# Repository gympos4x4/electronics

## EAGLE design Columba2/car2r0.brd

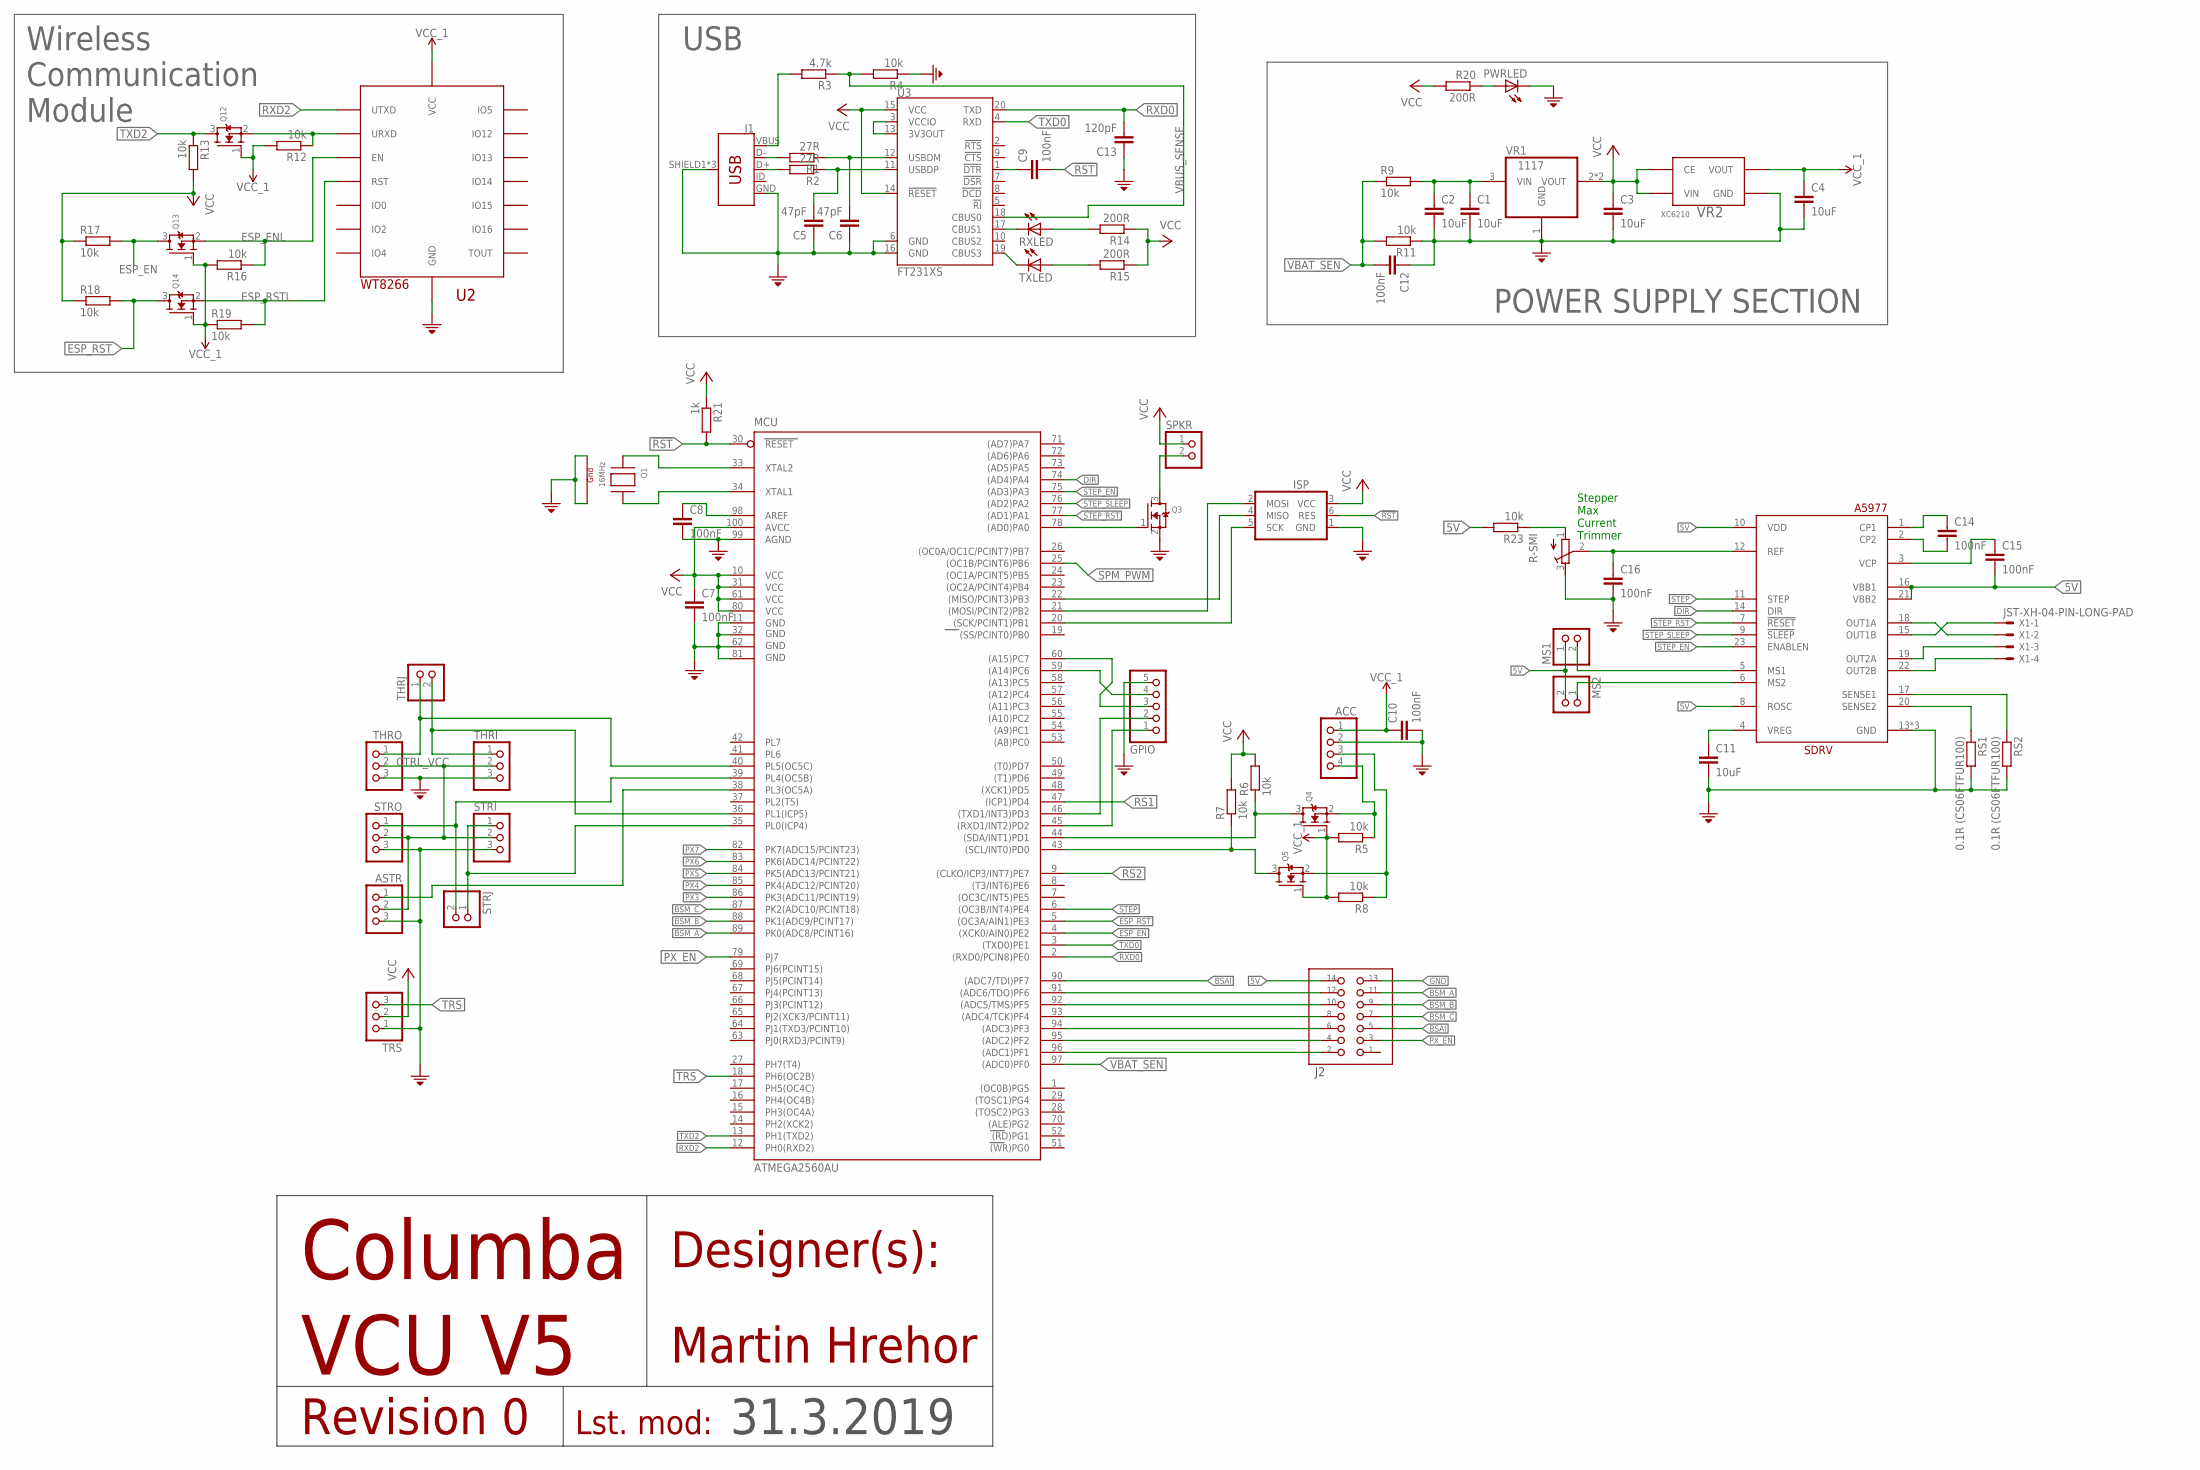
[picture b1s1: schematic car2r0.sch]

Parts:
ACC: PINHD-1X4/90; 1X04/90
ASTR: PINHD-1X3; 1X03
C1, C2, C3, C4, C11: 10uF; C1206
C5, C6: 47pF; C0603
C7, C8, C9, C10, C12, C14, C15, C16: 100nF; C1206
C13: 120pF; C0603
GPIO: PINHD-1X5; 1X05
ISP: ISP
J1: USB_MICRO-B_FEMALE-SMT; USB-B-MICRO-SMD
J2: DS1014-14S
MCU: ATMEGA2560AU; TQFP100
MS1, MS2: PINHD-1X2; 1X02
PWRLED: LEDCHIP-LED0603; CHIP-LED0603
Q1: 16MHz; NX3225
Q3, Q4, Q5, Q12, Q13, Q14: MOSFET-NREFLOW; SOT23
R1, R2: 27R; R0603
R3: 4.7k; R0603
R4, R5, R6, R7, R8, R12, R13, R16, R17, R18, R19, R23: 10k; R0603
R9, R11: 10k; R0805
R14, R15, R20: 200R; R0603
R21: 1k; R0603
R-SMI: R-TRIMM5W; RTRIM5W
RS1, RS2: 0.1R (CS06FTFUR100); R1206
RXLED: LEDCHIP-LED0603; CHIP-LED0603
SDRV: A4982LP; TSSOP24P
SPKR: PINHD-1X2; 1X02
STRI: PINHD-1X3; 1X03
STRJ: PINHD-1X2; 1X02
STRO: PINHD-1X3; 1X03
THRI: PINHD-1X3; 1X03
THRJ: PINHD-1X2; 1X02
THRO: PINHD-1X3; 1X03
TRS: PINHD-1X3; 1X03
TXLED: LEDCHIP-LED0603; CHIP-LED0603
U2: WT8266
U3: FT231XS; SSOP20_L
VR1: 1117; SOT223
VR2: XC6210; SOT25
X1: JST-XH-04-PIN-LONG-PAD; JST-XH-04-PACKAGE-LONG-PAD

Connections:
3V3: ACC.1, C4.1, C10.1, Q4.1 (G), Q5.1 (G), Q12.1 (G), Q13.1 (G), Q14.1 (G), R5.2, R8.2, R12.2, R16.2, R19.1, U2.3V3 (VCC), VR2.5 (VOUT)
5V: C3.1, C7.1, C15.2, ISP.3 (VCC), J2.P$14, MCU.10 (VCC), MCU.31 (VCC1), MCU.61 (VCC2), MCU.80 (VCC3), MCU.100 (AVCC), MS1.1, MS2.2, R6.2, R7.2, R13.2, R14.1, R15.1, R17.1, R18.1, R20.2, R21.1, R23.2, SDRV.8 (ROSC), SDRV.10 (VDD), SDRV.16 (VBB1), SDRV.21 (VBB2), SPKR.1, TRS.2, U3.14 (!RESET), U3.15 (VCC), VR1.2 (VOUT), VR1.4 (VOUT), VR2.1 (VIN), VR2.3 (CE)
!RST: C9.2, ISP.6 (RES), MCU.30 (RESET), R21.2
AREF: C8.1, MCU.98 (AREF)
ASTR: ASTR.1, MCU.38 (PL3(OC5A))
BSA0: J2.P$10, MCU.92 ((ADC5/TMS)PF5)
BSA1: J2.P$12, MCU.91 ((ADC6/TDO)PF6)
BSAI: J2.P$5, MCU.90 ((ADC7/TDI)PF7)
BSM_A: J2.P$11, MCU.89 (PK0(ADC8/PCINT16))
BSM_B: J2.P$9, MCU.88 (PK1(ADC9/PCINT17))
BSM_C: J2.P$7, MCU.87 (PK2(ADC10/PCINT18))
CP1: C14.1, SDRV.1 (CP1)
CP2: C14.2, SDRV.2 (CP2)
CTRL_VCC: ASTR.2, STRI.2, STRO.2, THRI.2, THRO.2
DIR: MCU.74 ((AD4)PA4), SDRV.14 (DIR)
DTR: C9.1, U3.1 (!DTR)
ESP_EN: MCU.4 ((XCK0/AIN0)PE2), Q13.3 (D), R17.2
ESP_ENL: Q13.2 (S), R16.1, U2.EN
ESP_RST: MCU.5 ((OC3A/AIN1)PE3), Q14.3 (D), R18.2
ESP_RSTL: Q14.2 (S), R19.2, U2.RST
GND: ACC.2, ASTR.3, C1.2, C2.2, C3.2, C4.2, C5.1, C6.1, C7.2, C8.2, C10.2, C11.2, C12.1, C13.1, C16.2, GPIO.5, ISP.1 (GND), J1.GND, J1.SHIELD1 (SHIELD), J1.SHIELD2 (SHIELD), J1.SHIELD3 (SHIELD), J2.P$13, MCU.11 (GND), MCU.32 (GND1), MCU.62 (GND2), MCU.81 (GND3), MCU.99 (AGND), PWRLED.C, Q1.2 (G2), Q1.4 (G1), Q3.2 (S), R4.1, R11.1, R-SMI.3 (E), RS1.2, RS2.2, SDRV.13 (GND), SDRV.24 (GND), SDRV.PAD (GND), STRI.3, STRO.3, THRI.3, THRO.3, TRS.1, U2.GND0 (GND), U2.GND1 (GND), U2.GND2 (GND), U3.6 (GND), U3.16 (GND), VR1.1 (GND), VR2.2 (GND)
LX0: J2.P$2, MCU.96 ((ADC1)PF1)
LX1: J2.P$4, MCU.95 ((ADC2)PF2)
LX2: J2.P$6, MCU.94 ((ADC3)PF3)
LX3: J2.P$8, MCU.93 ((ADC4/TCK)PF4)
MISO: ISP.4 (MISO), MCU.22 ((MISO/PCINT3)PB3)
MOSI: ISP.2 (MOSI), MCU.21 ((MOSI/PCINT2)PB2)
MS1: MS1.2, SDRV.5 (MS1)
MS2: MS2.1, SDRV.6 (MS2)
unnamed: MCU.33 (XTAL2), Q1.1 (X1)
unnamed: MCU.34 (XTAL1), Q1.3 (X2)
unnamed: GPIO.3, MCU.60 ((A15)PC7)
unnamed: GPIO.2, MCU.46 ((TXD1/INT3)PD3)
unnamed: GPIO.1, MCU.45 ((RXD1/INT2)PD2)
unnamed: PWRLED.A, R20.1
unnamed: GPIO.4, MCU.59 ((A14)PC6)
unnamed: R15.2, TXLED.A
unnamed: R14.2, RXLED.A
OUT1A: SDRV.18 (OUT1A), X1.2
OUT1B: SDRV.15 (OUT1B), X1.1
OUT2A: SDRV.19 (OUT2A), X1.3
OUT2B: SDRV.22 (OUT2B), X1.4
PX3: MCU.86 (PK3(ADC11/PCINT19))
PX4: MCU.85 (PK4(ADC12/PCINT20))
PX5: MCU.84 (PK5(ADC13/PCINT21))
PX6: MCU.83 (PK6(ADC14/PCINT22))
PX7: MCU.82 (PK7(ADC15/PCINT23))
PX_EN: J2.P$3, MCU.79 (PJ7)
RS1: MCU.47 ((ICP1)PD4)
RS2: MCU.9 ((CLKO/ICP3/INT7)PE7)
RXD0: C13.2, MCU.2 ((RXD0/PCIN8)PE0), U3.20 (TXD)
RXD2: MCU.12 (PH0(RXD2)), U2.UTXD
RXLED: RXLED.C, U3.17 (CBUS1)
SCK: ISP.5 (SCK), MCU.20 ((SCK/PCINT1)PB1)
SCL: MCU.43 ((SCL/INT0)PD0), Q5.3 (D), R7.1
SCLL: ACC.3, Q5.2 (S), R8.1
SDA: MCU.44 ((SDA/INT1)PD1), Q4.3 (D), R6.1
SDAL: ACC.4, Q4.2 (S), R5.1
SENSE1: RS2.1, SDRV.17 (SENSE1)
SENSE2: RS1.1, SDRV.20 (SENSE2)
SIV: R23.1, R-SMI.1 (A)
SPKR: MCU.78 ((AD0)PA0), Q3.1 (G)
SPKR0: Q3.3 (D), SPKR.2
SPM_PWM: MCU.25 ((OC1B/PCINT6)PB6)
STEP: MCU.6 ((OC3B/INT4)PE4), SDRV.11 (STEP)
STEP_EN: MCU.75 ((AD3)PA3), SDRV.23 (ENABLEN)
STEP_RST: MCU.77 ((AD1)PA1), SDRV.7 (!RESET)
STEP_SLEEP: MCU.76 ((AD2)PA2), SDRV.9 (!SLEEP)
STRI: MCU.35 (PL0(ICP4)), STRI.1, STRJ.1
STRO: MCU.39 (PL4(OC5B)), STRJ.2, STRO.1
SVREF: C16.1, R-SMI.2 (S), SDRV.12 (REF)
THRI: MCU.36 (PL1(ICP5)), THRI.1, THRJ.2
THRO: MCU.40 (PL5(OC5C)), THRJ.1, THRO.1
TRS: MCU.18 (PH6(OC2B)), TRS.3
TXD0: MCU.3 ((TXD0)PE1), U3.4 (RXD)
TXD2: MCU.13 (PH1(TXD2)), Q12.3 (D), R13.1
TXLED: TXLED.C, U3.19 (CBUS3)
URXD: Q12.2 (S), R12.1, U2.URXD
USBD+: J1.D+, R2.2
USBD-: J1.D-, R1.2
USBDM: C6.2, R1.1, U3.12 (USBDM)
USBDP: C5.2, R2.1, U3.11 (USBDP)
VBAT_SEN: C12.2, MCU.97 ((ADC0)PF0), R9.1, R11.2
VBUS: J1.VBUS, R3.2
VBUS_SENSE: R3.1, R4.2, U3.18 (CBUS0)
VCCIO: U3.3 (VCCIO), U3.13 (3V3OUT)
VCP: C15.1, SDRV.3 (VCP)
VIN: C1.1, C2.1, R9.2, VR1.3 (VIN)
VREG: C11.1, SDRV.4 (VREG)

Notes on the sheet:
POWER SUPPLY SECTION
Wireless Communication Module
USB
Columba
VCU V5
Revision 0
Designer(s):
Martin Hrehor
Lst. mod:
31.3.2019
Stepper Max Current Trimmer

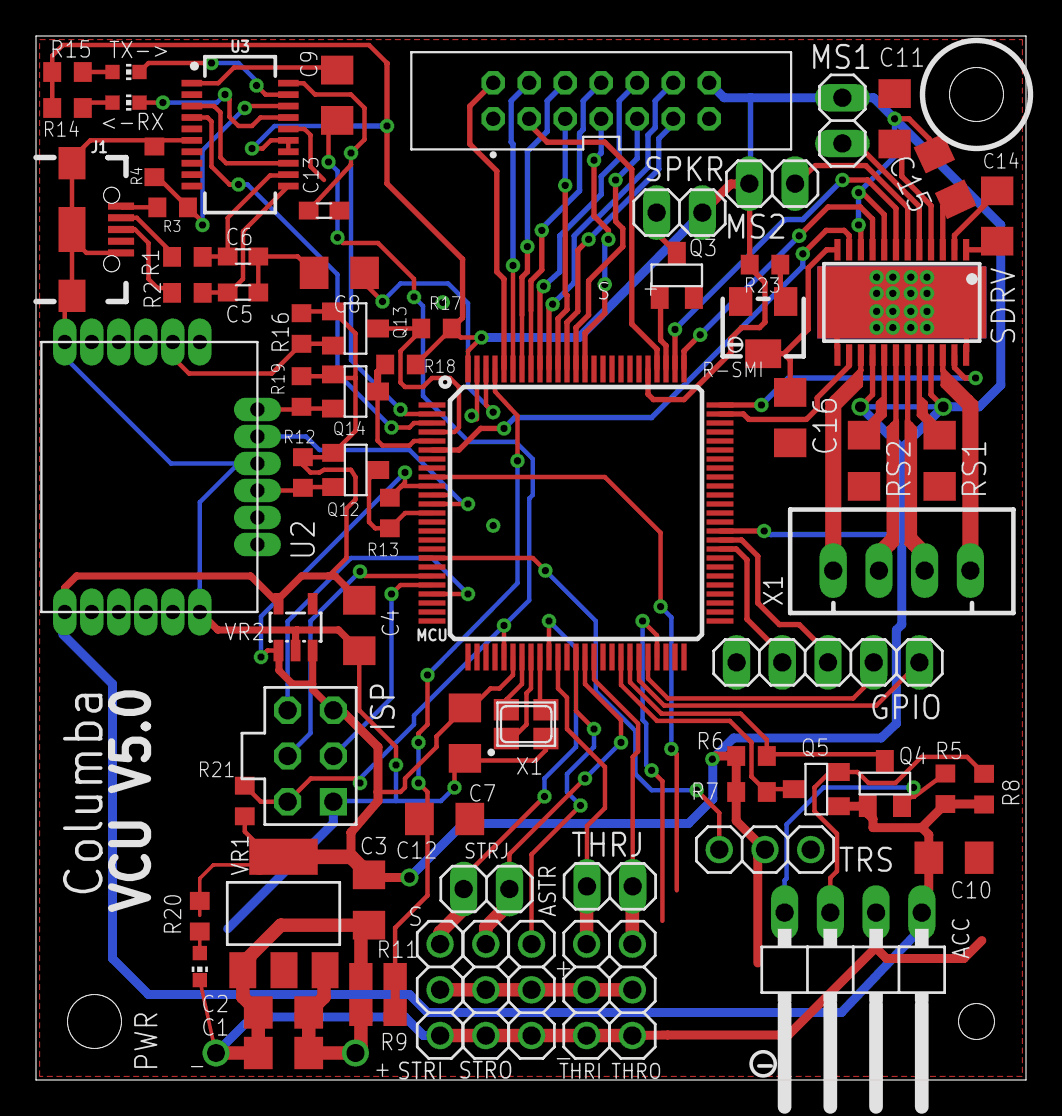
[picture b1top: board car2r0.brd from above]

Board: 2 copper layers, 55.0 x 58.0 mm, 73 parts (0 on the bottom side), 81 nets.

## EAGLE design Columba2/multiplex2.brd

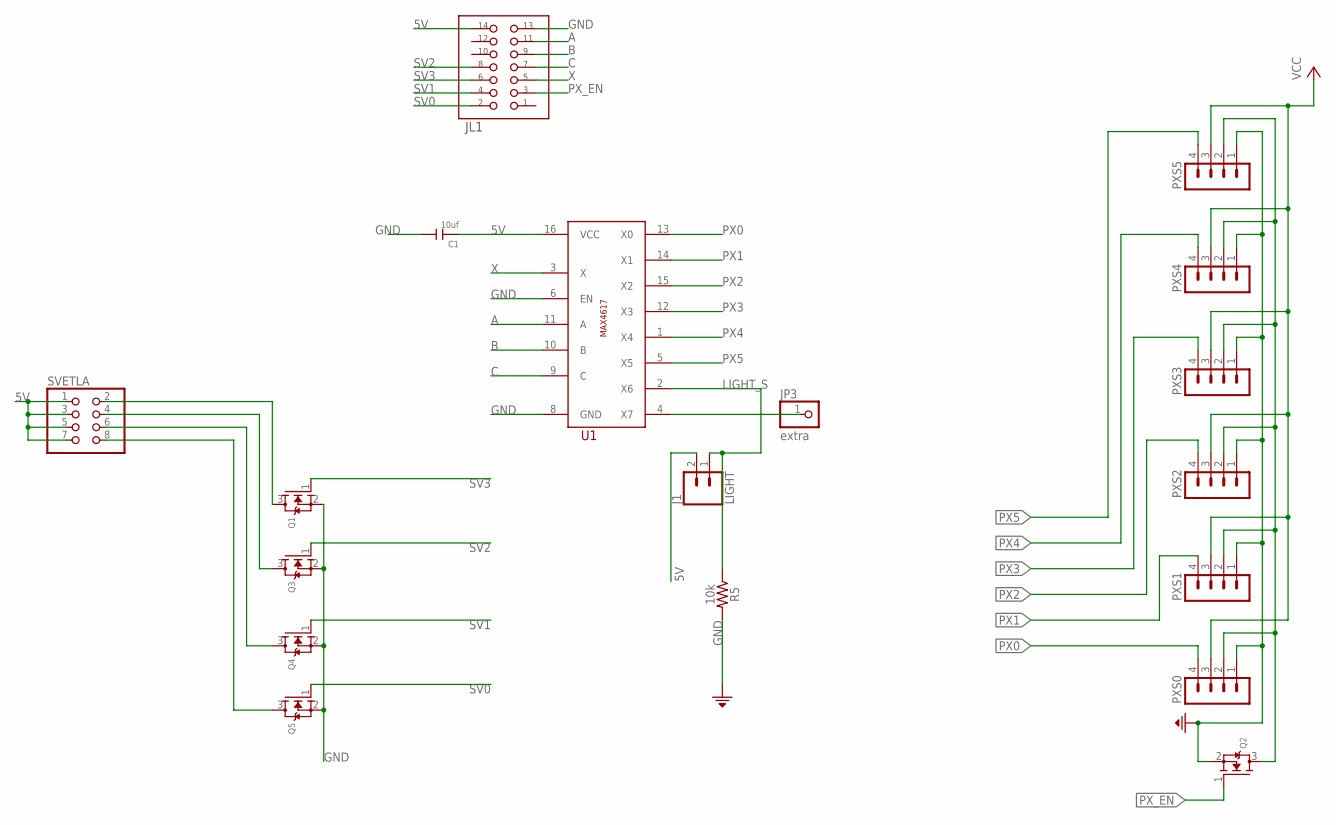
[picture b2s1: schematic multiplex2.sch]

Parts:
C1: 10uf; C1206
J1: LIGHT; 1X02
JL1: DS1014-14S
JP3: extra; 1X01
PXS0, PXS1, PXS2, PXS3, PXS4, PXS5: MA04-1
Q1, Q2, Q3, Q4, Q5: MOSFET-NREFLOW; SOT23
R5: 10k; 0603
SVETLA: PINHD-2X4; 2X04
U1: MAX4617CUE+T; TSSOP16

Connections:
5V: C1.1, J1.2, JL1.P$14, PXS0.3, PXS1.3, PXS2.3, PXS3.3, PXS4.3, PXS5.3, SVETLA.1, SVETLA.3, SVETLA.5, SVETLA.7, U1.16 (VCC)
A: JL1.P$11, U1.11 (A)
B: JL1.P$9, U1.10 (B)
C: JL1.P$7, U1.9 (C)
GND: C1.2, JL1.P$13, PXS0.1, PXS1.1, PXS2.1, PXS3.1, PXS4.1, PXS5.1, Q1.2 (S), Q2.2 (S), Q3.2 (S), Q4.2 (S), Q5.2 (S), R5.2, U1.6 (EN), U1.8 (GND)
LIGHT_S: J1.1, R5.1, U1.2 (X6)
unnamed: Q1.3 (D), SVETLA.2
unnamed: Q3.3 (D), SVETLA.4
unnamed: Q4.3 (D), SVETLA.6
unnamed: Q5.3 (D), SVETLA.8
unnamed: JP3.1, U1.4 (X7)
PX0: PXS0.4, U1.13 (X0)
PX1: PXS1.4, U1.14 (X1)
PX2: PXS2.4, U1.15 (X2)
PX3: PXS3.4, U1.12 (X3)
PX4: PXS4.4, U1.1 (X4)
PX5: PXS5.4, U1.5 (X5)
PXSO: PXS0.2, PXS1.2, PXS2.2, PXS3.2, PXS4.2, PXS5.2, Q2.3 (D)
PX_EN: JL1.P$3, Q2.1 (G)
SV0: JL1.P$2, Q5.1 (G)
SV1: JL1.P$4, Q4.1 (G)
SV2: JL1.P$8, Q3.1 (G)
SV3: JL1.P$6, Q1.1 (G)
X: JL1.P$5, U1.3 (X)

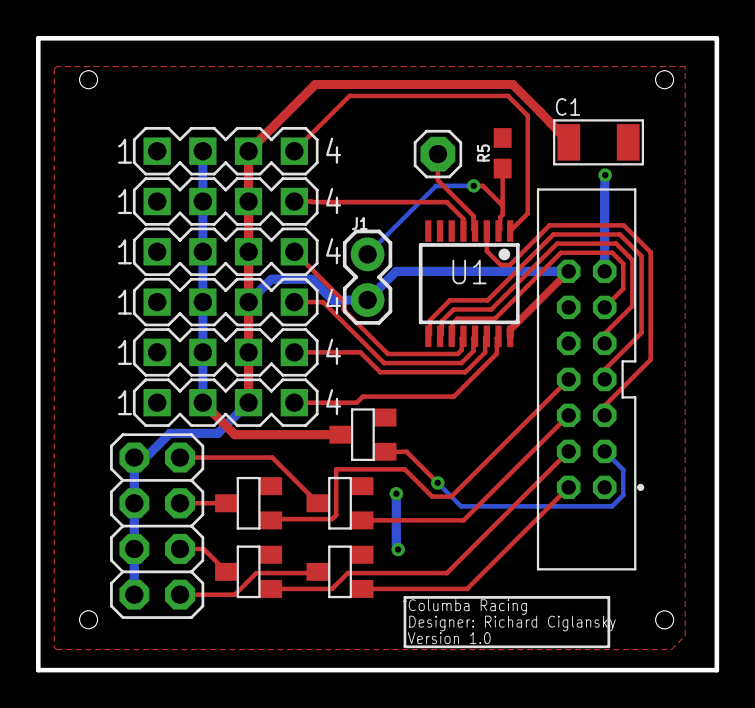
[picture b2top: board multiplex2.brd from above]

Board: 2 copper layers, 37.7 x 35.1 mm, 18 parts (0 on the bottom side), 24 nets.

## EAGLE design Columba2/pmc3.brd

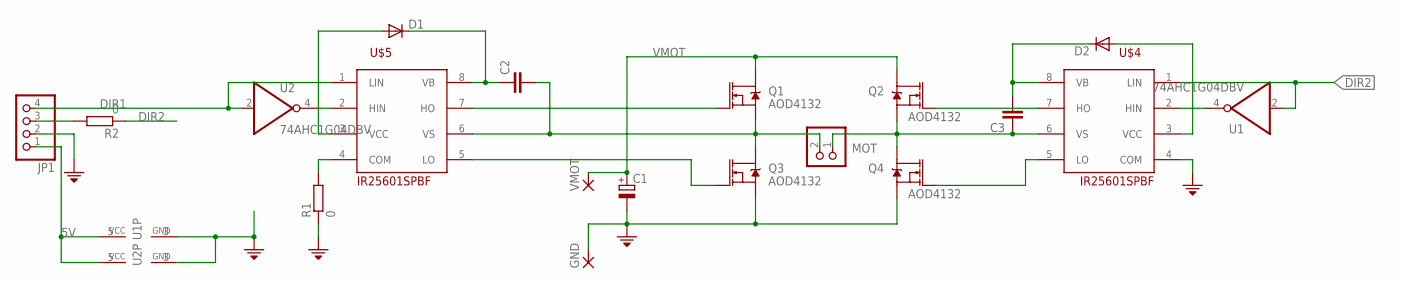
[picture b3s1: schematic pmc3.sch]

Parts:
C1: CPOL-EUE5-13; E5-13
C2, C3: C-EUC0805; C0805
D1, D2: DIODE-SOD123; SOD123
GND: SMD5; SMD2,54-5,08
JP1: PINHD-1X4/90; 1X04/90
MOT: PINHD-1X2; 1X02
Q1, Q2, Q3, Q4: AOD4132; DPAK
R1, R2: 0; R1206
U1, U2: 74AHC1G04DBV; SOT23-5
U$4, U$5: IR25601SPBF; SO08
VMOT: SMD5; SMD2,54-5,08

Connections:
5V: D1.A, D2.A, JP1.1, U1.5 (VCC), U2.5 (VCC), U$4.3 (VCC), U$5.3 (VCC)
D1O: C2.2, MOT.2, Q1.3 (S), Q3.4 (D), U$5.6 (VS)
D2O: C3.1, MOT.1, Q2.3 (S), Q4.4 (D), U$4.6 (VS)
DIR1: JP1.4, U2.2 (I), U$5.1 (LIN)
DIR2: R2.1, U1.2 (I), U$4.1 (LIN)
GND: C1.-, GND.1, JP1.2, Q3.3 (S), Q4.3 (S), R1.1, U1.3 (GND), U2.3 (GND), U$4.4 (COM)
unnamed: R1.2, U$5.4 (COM)
unnamed: JP1.3, R2.2
unnamed: Q3.1 (G), U$5.5 (LO)
unnamed: Q1.1 (G), U$5.7 (HO)
unnamed: U2.4 (O), U$5.2 (HIN)
unnamed: U1.4 (O), U$4.2 (HIN)
unnamed: Q4.1 (G), U$4.5 (LO)
unnamed: Q2.1 (G), U$4.7 (HO)
VBOOT1: C2.1, D1.C, U$5.8 (VB)
VBOOT2: C3.2, D2.C, U$4.8 (VB)
VMOT: C1.+, Q1.4 (D), Q2.4 (D), VMOT.1

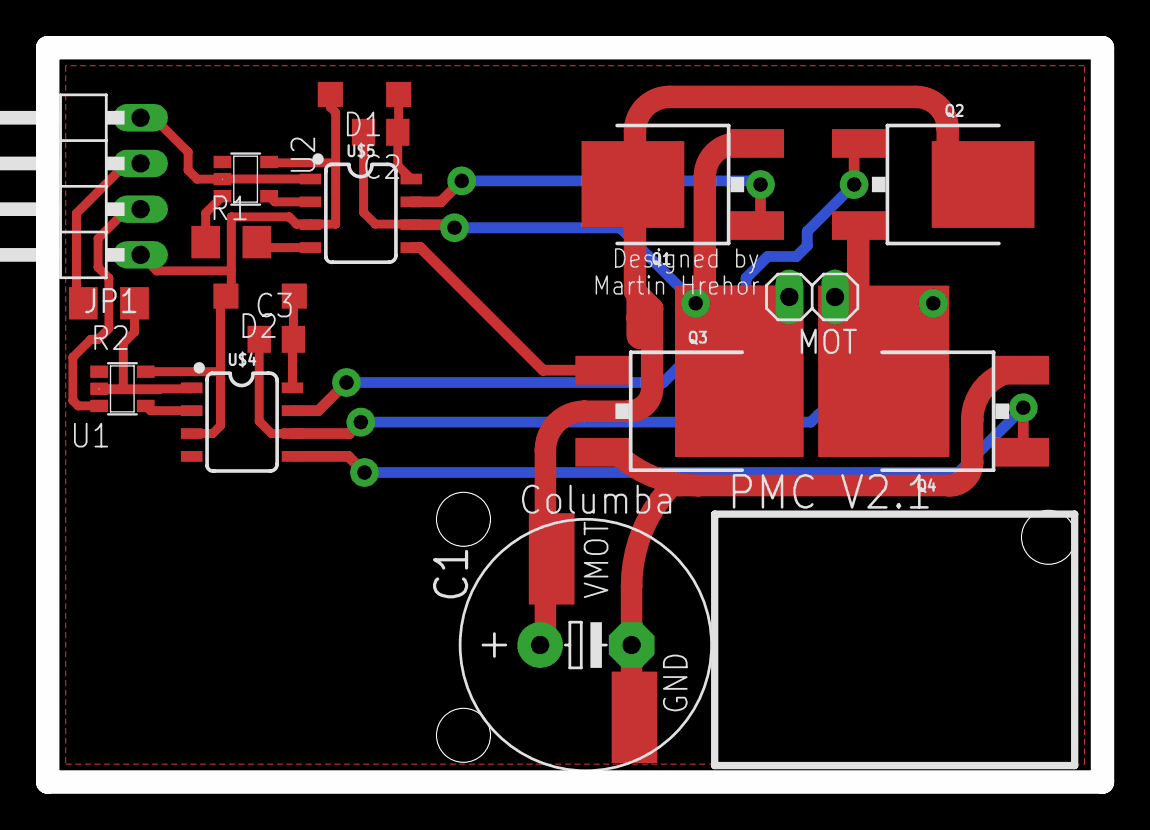
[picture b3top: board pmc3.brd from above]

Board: 2 copper layers, 58.6 x 40.8 mm, 19 parts (0 on the bottom side), 17 nets.

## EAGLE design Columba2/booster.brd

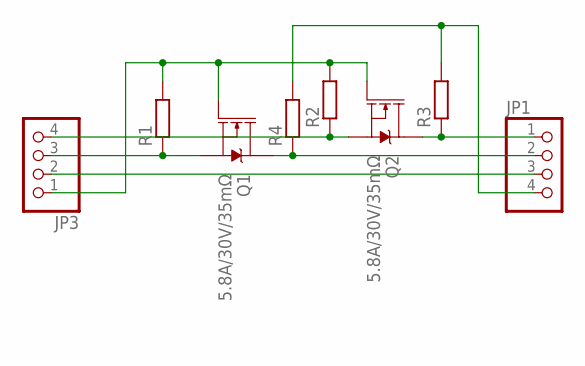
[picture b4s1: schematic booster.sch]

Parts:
JP1, JP3: PINHD-1X4/90; 1X04/90
Q1, Q2: 5.8A/30V/35mΩ; SOT23-3
R1, R2, R3, R4: R-EU_R0805; R0805

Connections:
unnamed: JP3.3, Q1.2 (S), R1.1
unnamed: JP1.2, Q1.3 (D), R4.1
unnamed: JP1.1, Q2.3 (D), R3.1
unnamed: JP3.4, Q2.2 (S), R2.1
unnamed: JP1.4, R3.2, R4.2
unnamed: JP1.3, JP3.2
unnamed: JP3.1, Q1.1 (G), Q2.1 (G), R1.2, R2.2

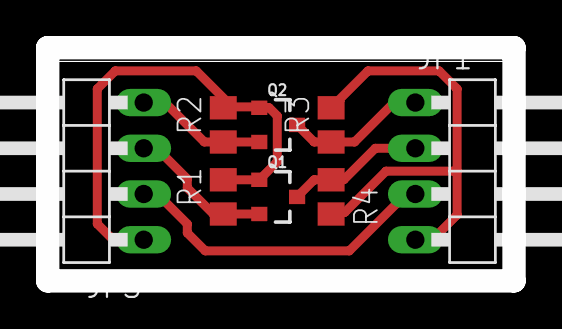
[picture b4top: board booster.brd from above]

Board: 2 copper layers, 25.9 x 13.0 mm, 8 parts (0 on the bottom side), 7 nets.

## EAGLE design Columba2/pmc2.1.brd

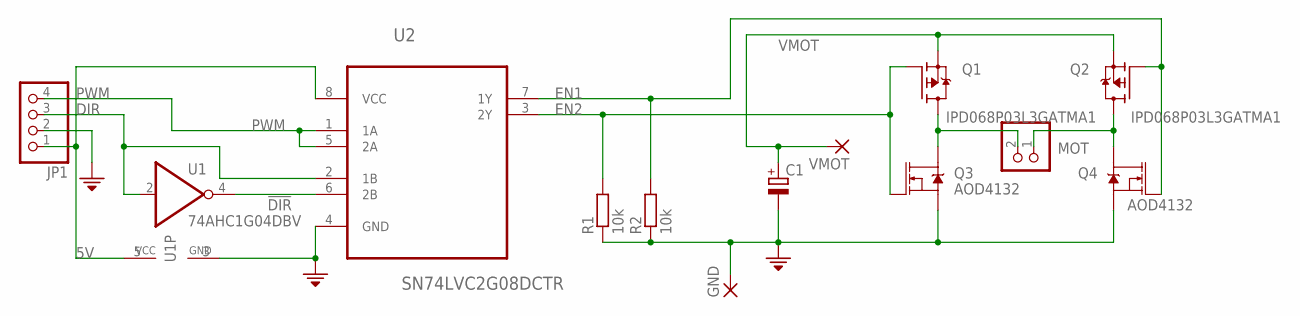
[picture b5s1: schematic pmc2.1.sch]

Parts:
C1: CPOL-EUE5-13; E5-13
GND: SMD5; SMD2,54-5,08
JP1: PINHD-1X4/90; 1X04/90
MOT: PINHD-1X2; 1X02
Q1, Q2: IPD068P03L3GATMA1; TO252
Q3, Q4: AOD4132; DPAK
R1, R2: 10k; R0603
U1: 74AHC1G04DBV; SOT23-5
U2: SN74LVC2G08DCTR; SOP65P400X130-8N
VMOT: SMD5; SMD2,54-5,08

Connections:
5V: JP1.1, U1.5 (VCC), U2.8 (VCC)
!DIR: U1.4 (O), U2.6 (2B)
DIR: JP1.3, U1.2 (I), U2.2 (1B)
EN1: Q2.1 (G), Q4.1 (G), R2.2, U2.7 (1Y)
EN2: Q1.1 (G), Q3.1 (G), R1.2, U2.3 (2Y)
GND: C1.-, GND.1, JP1.2, Q3.3 (S), Q4.3 (S), R1.1, R2.1, U1.3 (GND), U2.4 (GND)
unnamed: MOT.2, Q1.3 (D), Q3.4 (D)
unnamed: MOT.1, Q2.3 (D), Q4.4 (D)
PWM: JP1.4, U2.1 (1A), U2.5 (2A)
VMOT: C1.+, Q1.2 (S), Q2.2 (S), VMOT.1

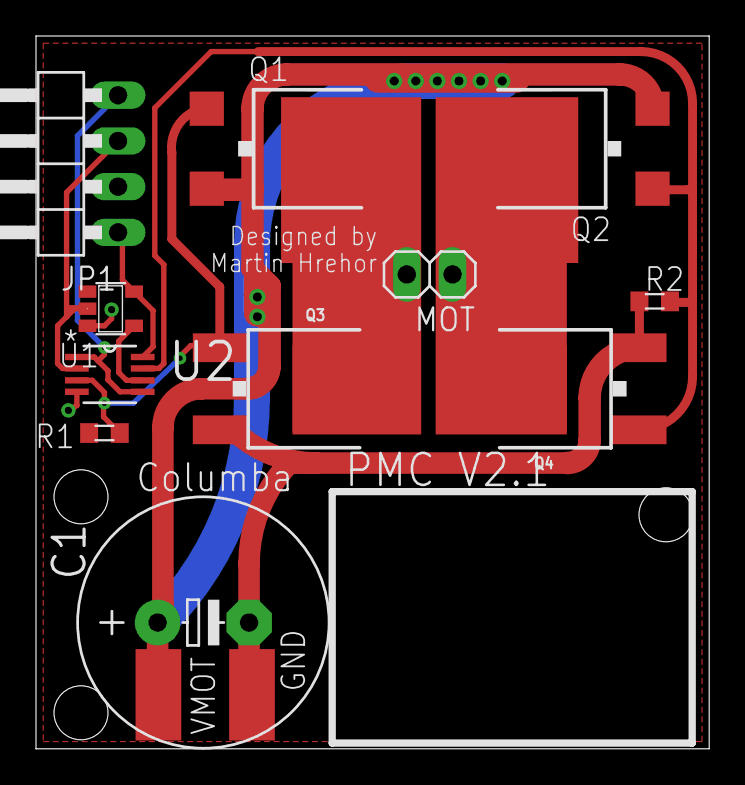
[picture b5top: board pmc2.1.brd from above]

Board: 2 copper layers, 37.4 x 39.6 mm, 13 parts (0 on the bottom side), 10 nets.

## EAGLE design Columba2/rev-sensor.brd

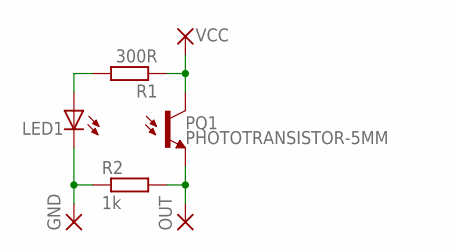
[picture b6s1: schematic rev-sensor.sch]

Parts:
GND: WIREPADSMD5-1,8; 5-1,8
LED1: LED5MM
OUT: WIREPADSMD5-1,8; 5-1,8
PQ1: PHOTOTRANSISTOR-5MM; LED5MM
R1: 300R; R0805
R2: 1k; R0805
VCC: WIREPADSMD5-1,8; 5-1,8

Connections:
GND: GND.1, LED1.K (C), R2.1
unnamed: LED1.A, R1.2
OUT: OUT.1, PQ1.A (E), R2.2
VCC: PQ1.K (C), R1.1, VCC.1

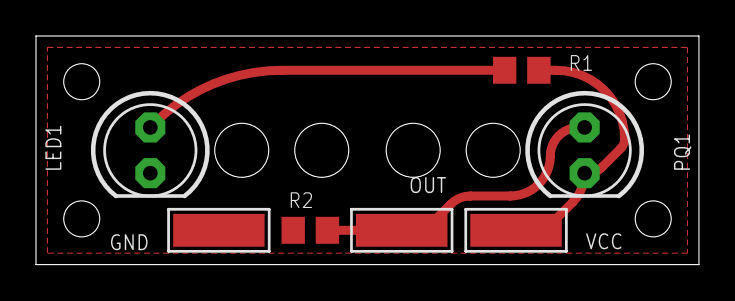
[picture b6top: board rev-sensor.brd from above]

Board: 2 copper layers, 36.8 x 12.7 mm, 7 parts (0 on the bottom side), 4 nets.

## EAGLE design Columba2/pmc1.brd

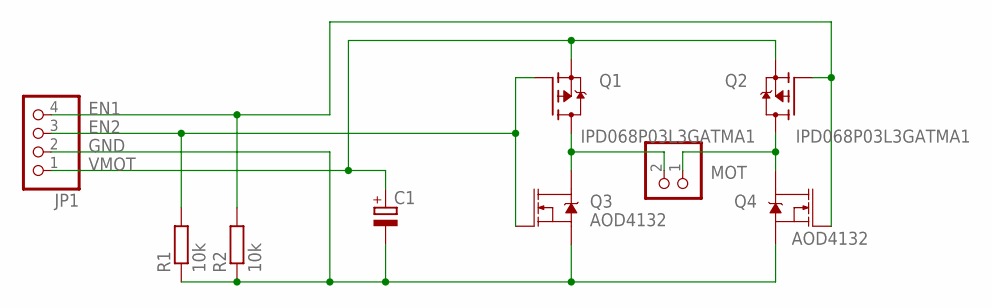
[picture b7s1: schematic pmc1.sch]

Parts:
C1: CPOL-EUE5-13; E5-13
JP1: PINHD-1X4/90; 1X04/90
MOT: PINHD-1X2; 1X02
Q1, Q2: IPD068P03L3GATMA1; TO252
Q3, Q4: AOD4132; DPAK
R1, R2: 10k; R0603

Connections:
EN1: JP1.4, Q2.1 (G), Q4.1 (G), R2.2
EN2: JP1.3, Q1.1 (G), Q3.1 (G), R1.2
GND: C1.-, JP1.2, Q3.3 (S), Q4.3 (S), R1.1, R2.1
unnamed: MOT.2, Q1.3 (D), Q3.4 (D)
unnamed: MOT.1, Q2.3 (D), Q4.4 (D)
VMOT: C1.+, JP1.1, Q1.2 (S), Q2.2 (S)

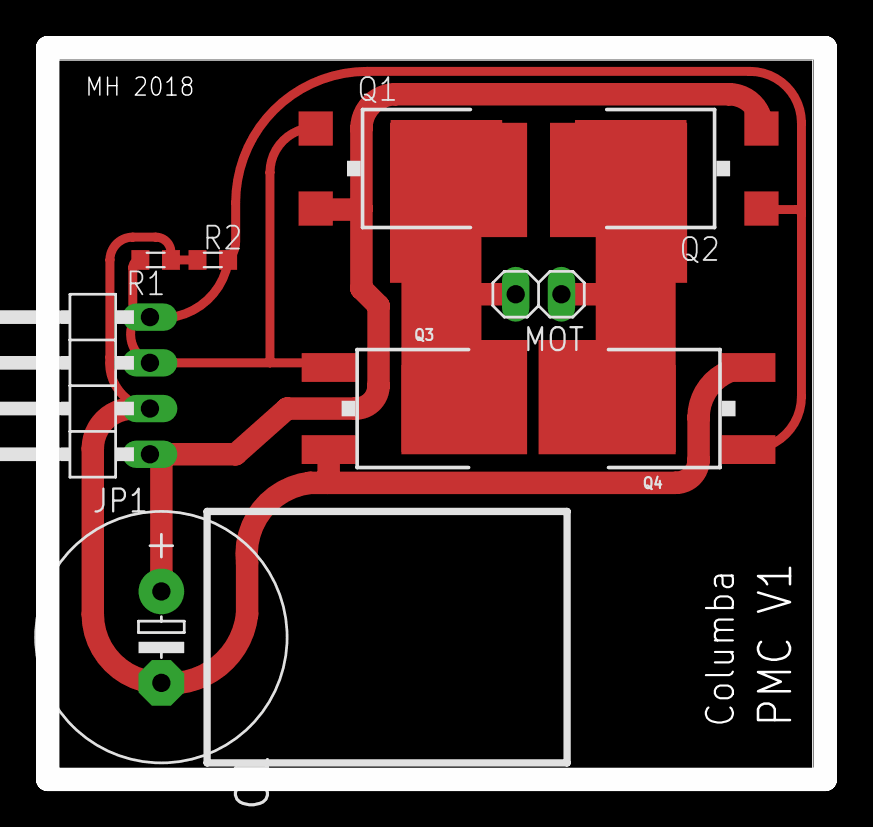
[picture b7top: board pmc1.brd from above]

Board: 2 copper layers, 43.2 x 40.6 mm, 9 parts (0 on the bottom side), 6 nets.

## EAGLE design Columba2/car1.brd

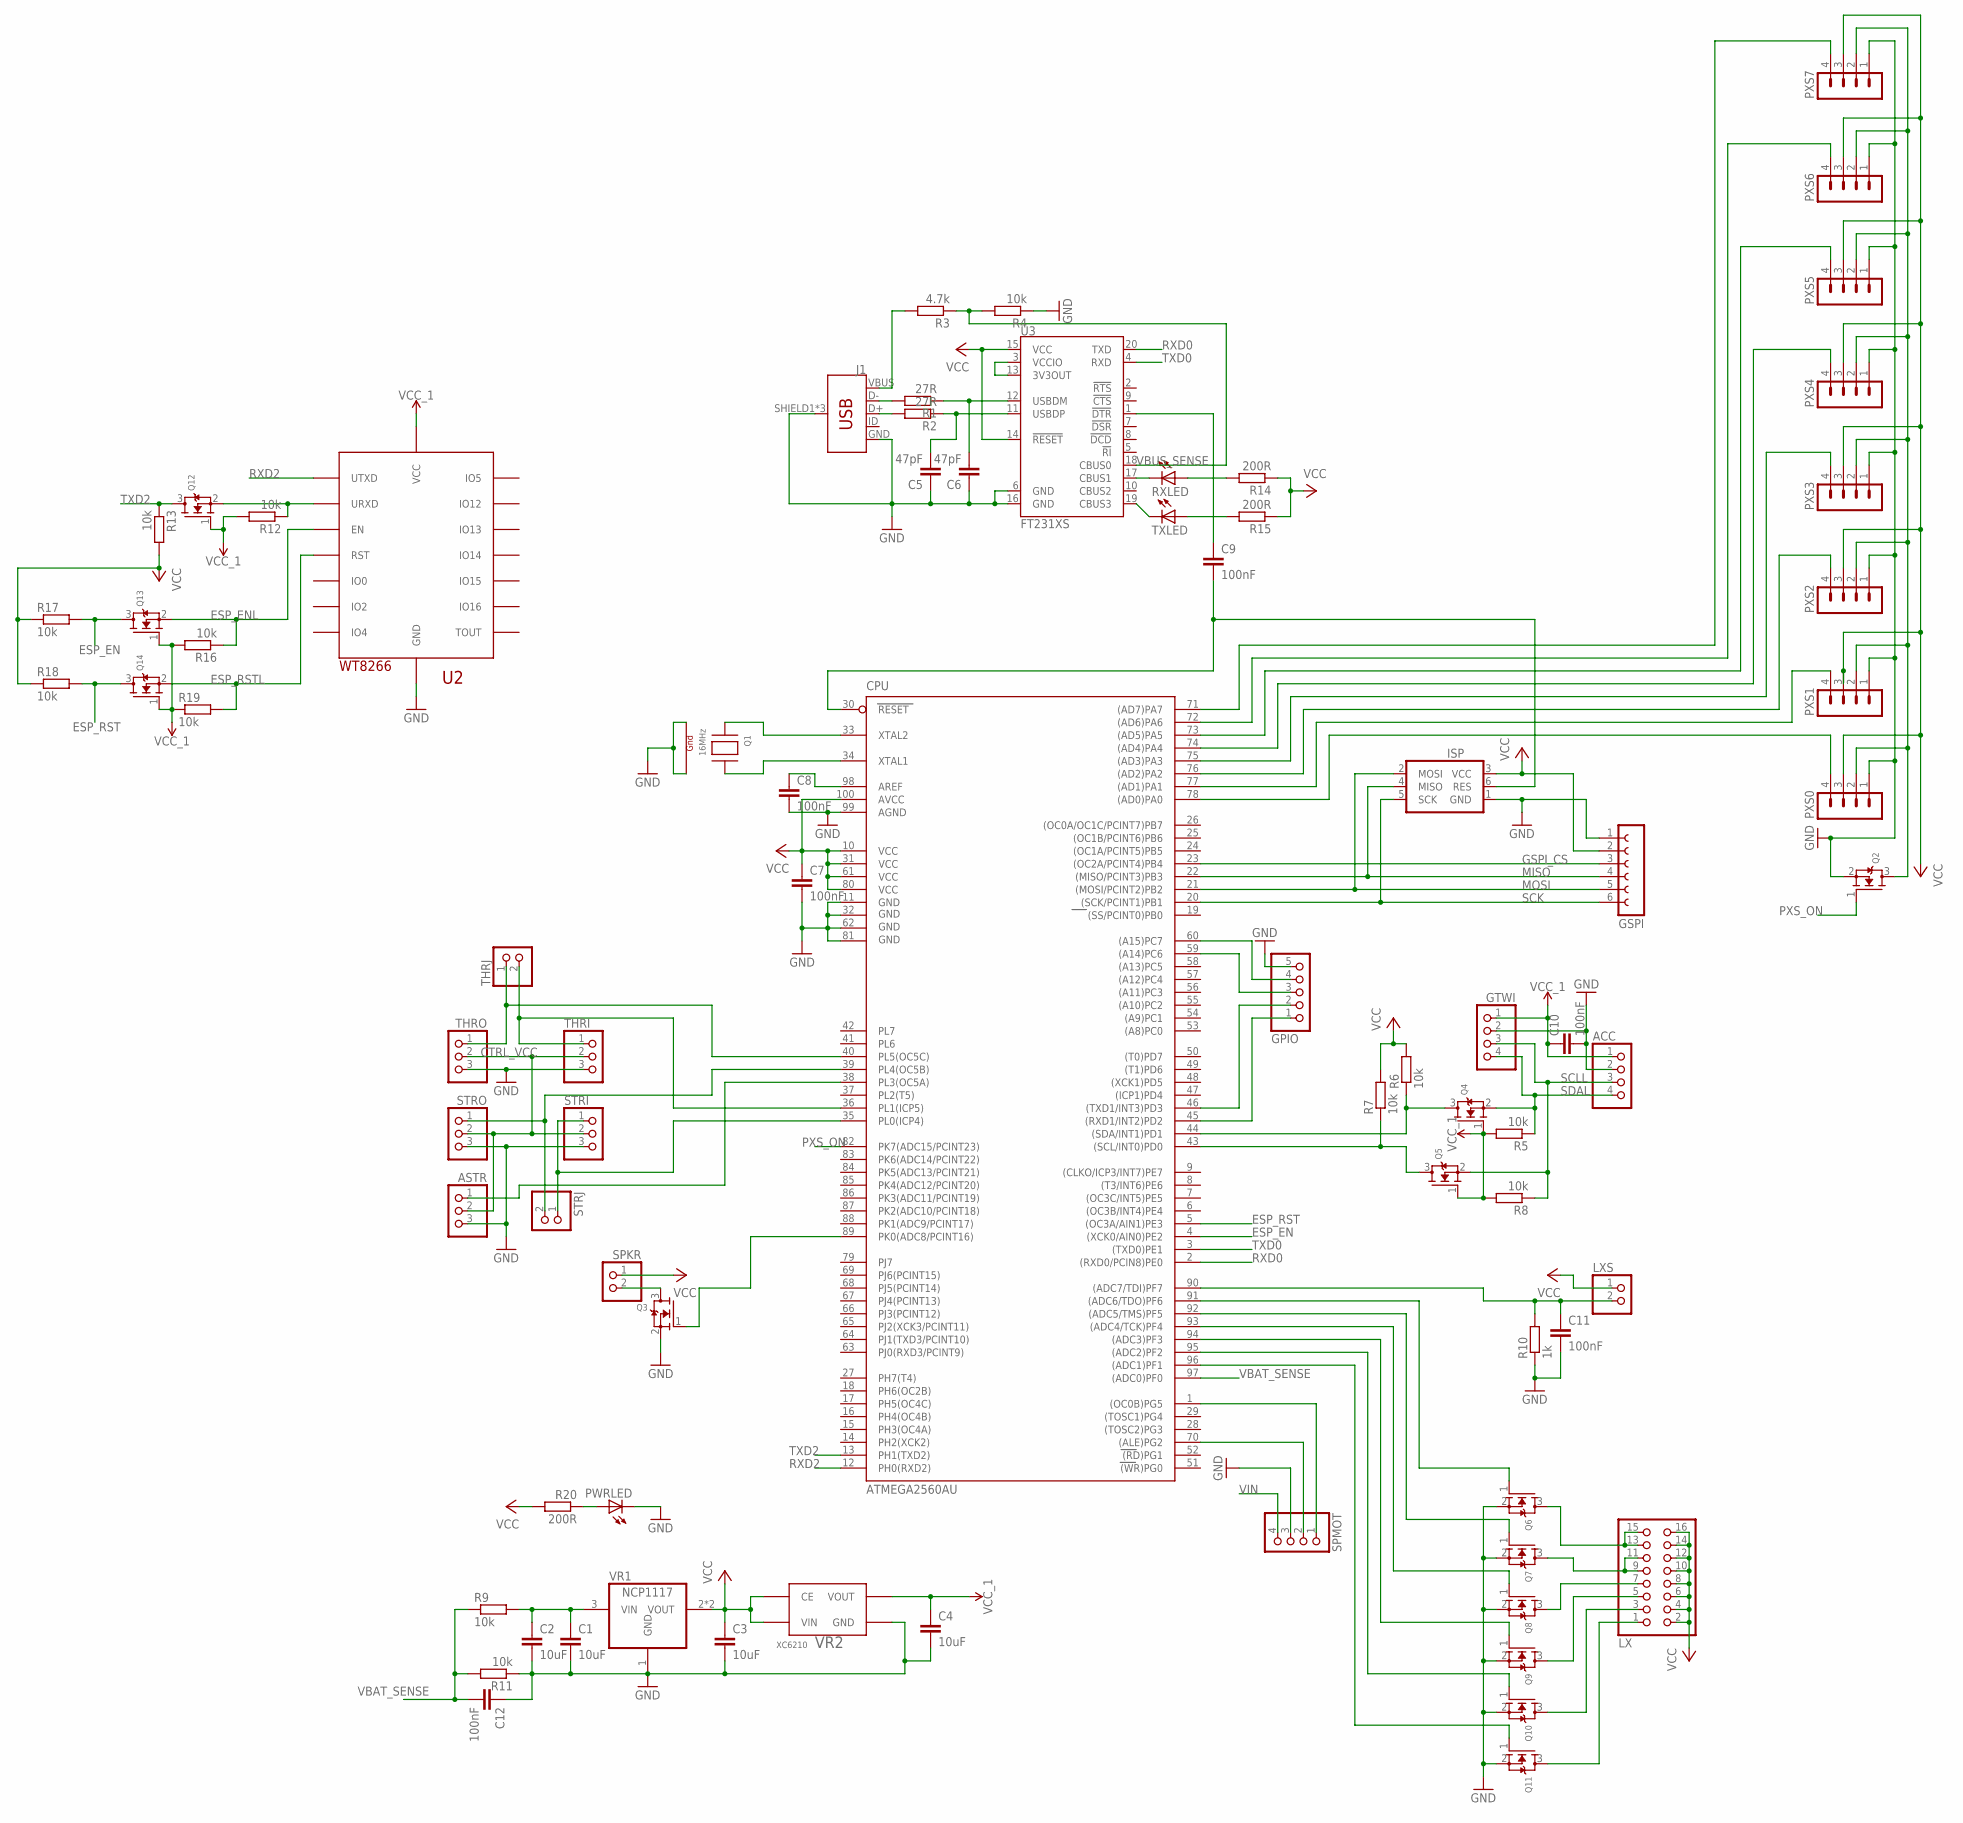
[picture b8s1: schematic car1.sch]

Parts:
ACC: PINHD-1X4; 1X04
ASTR: PINHD-1X3; 1X03
C1, C2, C3, C4: 10uF; C1206
C5, C6: 47pF; C0603
C7, C8, C9, C10, C11, C12: 100nF; C1206
CPU: ATMEGA2560AU; TQFP100
GPIO: PINHD-1X5; 1X05
GSPI: FE06W
GTWI: PINHD-1X4/90; 1X04/90
ISP: ISP
J1: USB_MICRO-B_FEMALE-SMT; USB-B-MICRO-SMD
LX: PINHD-2X8; 2X08
LXS: PINHD-1X2; 1X02
PWRLED: LEDCHIP-LED0603; CHIP-LED0603
PXS0, PXS1, PXS2, PXS3, PXS4, PXS5, PXS6, PXS7: MA04-1
Q1: 16MHz; NX3225
Q2, Q3, Q4, Q5, Q6, Q7, Q8, Q9, Q10, Q11, Q12, Q13, Q14: MOSFET-NREFLOW; SOT23
R1, R2: 27R; R0603
R3: 4.7k; R0603
R4, R5, R6, R7, R8, R12, R13, R16, R17, R18, R19: 10k; R0603
R9, R11: 10k; R0805
R10: 1k; R0603
R14, R15, R20: 200R; R0603
RXLED: LEDCHIP-LED0603; CHIP-LED0603
SPKR: PINHD-1X2; 1X02
SPMOT: PINHD-1X4/90; 1X04/90
STRI: PINHD-1X3; 1X03
STRJ: PINHD-1X2; 1X02
STRO: PINHD-1X3; 1X03
THRI: PINHD-1X3; 1X03
THRJ: PINHD-1X2; 1X02
THRO: PINHD-1X3; 1X03
TXLED: LEDCHIP-LED0603; CHIP-LED0603
U2: WT8266
U3: FT231XS; SSOP20_L
VR1: NCP1117; SOT223
VR2: XC6210; SOT25

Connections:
!RST: C9.2, CPU.30 (RESET), ISP.6 (RES)
AREF: C8.1, CPU.98 (AREF)
ASTR: ASTR.1, CPU.38 (PL3(OC5A))
CTRL_VCC: ASTR.2, STRI.2, STRO.2, THRI.2, THRO.2
DTR: C9.1, U3.1 (!DTR)
ESP_EN: CPU.4 ((XCK0/AIN0)PE2), Q13.3 (D), R17.2
ESP_ENL: Q13.2 (S), R16.1, U2.EN
ESP_RST: CPU.5 ((OC3A/AIN1)PE3), Q14.3 (D), R18.2
ESP_RSTL: Q14.2 (S), R19.2, U2.RST
GND: ACC.2, ASTR.3, C1.2, C2.2, C3.2, C4.2, C5.1, C6.1, C7.2, C8.2, C10.2, C11.2, C12.1, CPU.11 (GND), CPU.32 (GND1), CPU.62 (GND2), CPU.81 (GND3), CPU.99 (AGND), GPIO.5, GSPI.1, GTWI.2, ISP.1 (GND), J1.GND, J1.SHIELD1 (SHIELD), J1.SHIELD2 (SHIELD), J1.SHIELD3 (SHIELD), PWRLED.C, PXS0.1, PXS1.1, PXS2.1, PXS3.1, PXS4.1, PXS5.1, PXS6.1, PXS7.1, Q1.2 (G2), Q1.4 (G1), Q2.2 (S), Q3.2 (S), Q6.2 (S), Q7.2 (S), Q8.2 (S), Q9.2 (S), Q10.2 (S), Q11.2 (S), R4.1, R10.1, R11.1, SPMOT.3, STRI.3, STRO.3, THRI.3, THRO.3, U2.GND0 (GND), U2.GND1 (GND), U2.GND2 (GND), U3.6 (GND), U3.16 (GND), VR1.1 (GND), VR2.2 (GND)
GSPI_CS: CPU.23 ((OC2A/PCINT4)PB4), GSPI.3
LX0: CPU.96 ((ADC1)PF1), Q11.1 (G)
LX1: CPU.95 ((ADC2)PF2), Q10.1 (G)
LX2: CPU.94 ((ADC3)PF3), Q9.1 (G)
LX3: CPU.93 ((ADC4/TCK)PF4), Q8.1 (G)
LX4: CPU.92 ((ADC5/TMS)PF5), Q7.1 (G)
LX5: CPU.91 ((ADC6/TDO)PF6), Q6.1 (G)
LXS: C11.1, CPU.90 ((ADC7/TDI)PF7), LXS.2, R10.2
MISO: CPU.22 ((MISO/PCINT3)PB3), GSPI.4, ISP.4 (MISO)
MOSI: CPU.21 ((MOSI/PCINT2)PB2), GSPI.5, ISP.2 (MOSI)
unnamed: CPU.33 (XTAL2), Q1.1 (X1)
unnamed: CPU.34 (XTAL1), Q1.3 (X2)
unnamed: CPU.60 ((A15)PC7), GPIO.4
unnamed: CPU.59 ((A14)PC6), GPIO.3
unnamed: CPU.46 ((TXD1/INT3)PD3), GPIO.2
unnamed: CPU.45 ((RXD1/INT2)PD2), GPIO.1
unnamed: PWRLED.A, R20.1
unnamed: R15.2, TXLED.A
unnamed: R14.2, RXLED.A
unnamed: CPU.78 ((AD0)PA0), PXS0.4
unnamed: CPU.77 ((AD1)PA1), PXS1.4
unnamed: LX.13, LX.15, Q6.3 (D)
unnamed: LX.9, LX.11, Q7.3 (D)
unnamed: CPU.76 ((AD2)PA2), PXS2.4
unnamed: LX.7, Q8.3 (D)
unnamed: LX.5, Q9.3 (D)
unnamed: LX.3, Q10.3 (D)
unnamed: LX.1, Q11.3 (D)
unnamed: CPU.75 ((AD3)PA3), PXS3.4
unnamed: CPU.74 ((AD4)PA4), PXS4.4
unnamed: CPU.73 ((AD5)PA5), PXS5.4
unnamed: CPU.72 ((AD6)PA6), PXS6.4
unnamed: CPU.71 ((AD7)PA7), PXS7.4
PXSO: PXS0.2, PXS1.2, PXS2.2, PXS3.2, PXS4.2, PXS5.2, PXS6.2, PXS7.2, Q2.3 (D)
PXS_ON: CPU.82 (PK7(ADC15/PCINT23)), Q2.1 (G)
RXD0: CPU.2 ((RXD0/PCIN8)PE0), U3.20 (TXD)
RXD2: CPU.12 (PH0(RXD2)), U2.UTXD
RXLED: RXLED.C, U3.17 (CBUS1)
SCK: CPU.20 ((SCK/PCINT1)PB1), GSPI.6, ISP.5 (SCK)
SCL: CPU.43 ((SCL/INT0)PD0), Q5.3 (D), R7.1
SCLL: ACC.3, GTWI.3, Q5.2 (S), R8.1
SDA: CPU.44 ((SDA/INT1)PD1), Q4.3 (D), R6.1
SDAL: ACC.4, GTWI.4, Q4.2 (S), R5.1
SPKR: CPU.89 (PK0(ADC8/PCINT16)), Q3.1 (G)
SPKR0: Q3.3 (D), SPKR.2
SPM_DIR: CPU.70 ((ALE)PG2), SPMOT.2
SPM_PWM: CPU.1 ((OC0B)PG5), SPMOT.1
STRI: CPU.35 (PL0(ICP4)), STRI.1, STRJ.1
STRO: CPU.39 (PL4(OC5B)), STRJ.2, STRO.1
THRI: CPU.36 (PL1(ICP5)), THRI.1, THRJ.2
THRO: CPU.40 (PL5(OC5C)), THRJ.1, THRO.1
TXD0: CPU.3 ((TXD0)PE1), U3.4 (RXD)
TXD2: CPU.13 (PH1(TXD2)), Q12.3 (D), R13.1
TXLED: TXLED.C, U3.19 (CBUS3)
URXD: Q12.2 (S), R12.1, U2.URXD
USBD+: J1.D+, R2.2
USBD-: J1.D-, R1.2
USBDM: C6.2, R1.1, U3.12 (USBDM)
USBDP: C5.2, R2.1, U3.11 (USBDP)
VBAT_SENSE: C12.2, CPU.97 ((ADC0)PF0), R9.1, R11.2
VBUS: J1.VBUS, R3.2
VBUS_SENSE: R3.1, R4.2, U3.18 (CBUS0)
VCC: C3.1, C7.1, CPU.10 (VCC), CPU.31 (VCC1), CPU.61 (VCC2), CPU.80 (VCC3), CPU.100 (AVCC), GSPI.2, ISP.3 (VCC), LX.2, LX.4, LX.6, LX.8, LX.10, LX.12, LX.14, LX.16, LXS.1, PXS0.3, PXS1.3, PXS2.3, PXS3.3, PXS4.3, PXS5.3, PXS6.3, PXS7.3, R6.2, R7.2, R13.2, R14.1, R15.1, R17.1, R18.1, R20.2, SPKR.1, U3.14 (!RESET), U3.15 (VCC), VR1.2 (VOUT), VR1.4 (VOUT), VR2.1 (VIN), VR2.3 (CE)
VCCIO: U3.3 (VCCIO), U3.13 (3V3OUT)
VCC_1: ACC.1, C4.1, C10.1, GTWI.1, Q4.1 (G), Q5.1 (G), Q12.1 (G), Q13.1 (G), Q14.1 (G), R5.2, R8.2, R12.2, R16.2, R19.1, U2.3V3 (VCC), VR2.5 (VOUT)
VIN: C1.1, C2.1, R9.2, SPMOT.4, VR1.3 (VIN)

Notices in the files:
parts and their libraries:
SparkFun-DiscreteSemi: Licensing: Creative Commons ShareAlike 4.0 International - https://creativecommons.org/licenses/by-sa/4.0
